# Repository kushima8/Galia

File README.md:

# Galia
Split 61-key ergo keyboard with trackball on right-hand side.

## Disclaimer
The layout is based on the [Ergodash](https://github.com/omkbd/ErgoDash) layout with the inner-most keys removed and a modified thumb cluster on the left hand side, and integrated 34mm trackball on the right. The Pro Micro position was also moved inwards to allow for a thinner board. The Ergodash layout was only used as a reference, nothing was copied and the board is a completely new design. Finally, the mechanical design of the [aball](https://github.com/brickbots/aball) was referenced for the design of the trackball mount, but an entirely new design was created.

## Key Features
* Slim design, or as slim as I could get while using standard MX-style Switches. Essentially, the Pro Micro or whatever other microcontroller used mounts under the PCB, flush and facing up with the help of a cutout.
* SMK MX-style switch support, solder only but the holes are mill-max socket compatible.
* OLED support, either using a standard 0.91" SSD1306 OLED or the [Crenshaw](https://github.com/Ariamelon/Crenshaw) 1.3" OLED breakout board.
* Single rotary encoder position replacing the top-most switch of the left thumb cluster.
* 34mm trackball on the right-hand side using the [Ogen](https://github.com/Ariamelon/Ogen) PMW3360 sensor board. Also compatible with [Jack's](https://www.tindie.com/products/jkicklighter/pmw3360-motion-sensor/) version. 
* Useable in both wired and wireless modes.
* Supports either charger on the microcontroller board or an external TP4056-based charger for faster charging. the TP4056 charger is also flush-mounted sitting up and supports the use of 0305 or 7305 mill-max hotswap sockets if desired.
* Case design with plate included with in-built 10° tent. Plate assumes use of the Crenshaw.
* Supports a massive battery due to the large space in the case. I'm personally using 18650 batteries. Go a year without charging!

## Changelog
* 02/10/2020: Initial commit with case.
* 06/10/2020: Added spot for external TP4056 charger board.
* 10/10/2020: Changed reset switch footprint and position, removed useless pull-up resistor.
* 11/10/2020: Now uses much less plastic and the position of the trackball was moved inwards and downwards.

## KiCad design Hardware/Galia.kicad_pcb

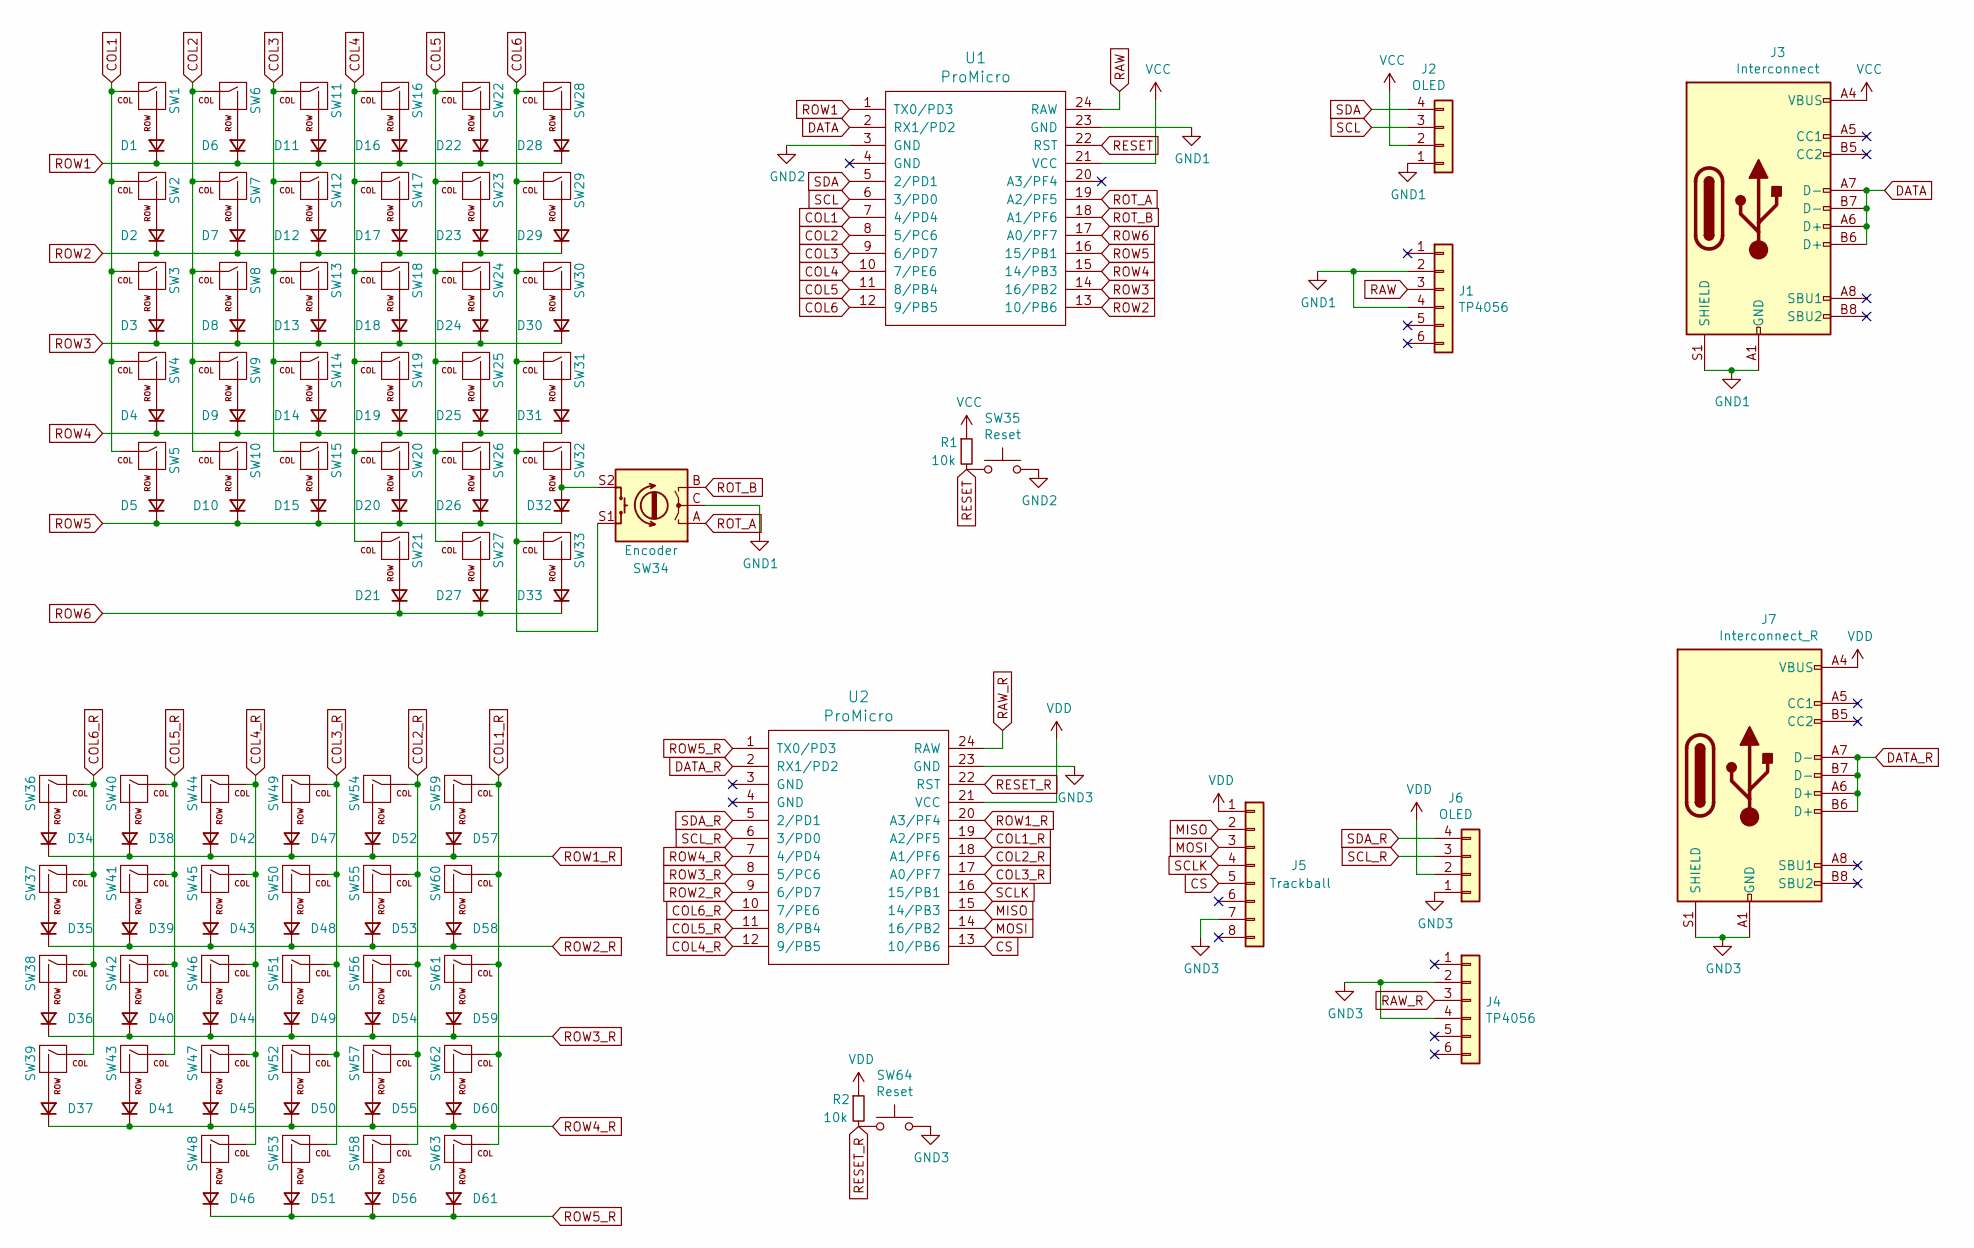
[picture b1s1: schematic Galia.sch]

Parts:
D1, D2, D3, D4, D5, D6, D7, D8, D9, D10, D11, D12, D13, D14, D15, D16, D17, D18, D19, D20, D21, D22, D23, D24, D25, D26, D27, D28, D29, D30, D31, D32, D33, D34, D35, D36, D37, D38, D39, D40, D41, D42, D43, D44, D45, D46, D47, D48, D49, D50, D51, D52, D53, D54, D55, D56, D57, D58, D59, D60, D61: D; D_SOD-123
J1, J4: TP4056; TP4056-18650
J2, J6: OLED; PinHeader_1x04_P2.54mm_Vertical_No_Silk
J3: Interconnect; USB-C-C168688
J5: Trackball; PinHeader_1x08_P2.54mm_Vertical
J7: Interconnect_R; USB-C-C168688
R1, R2: 10k; R_0603_1608Metric_Pad1.05x0.95mm_HandSolder
SW1, SW2, SW3, SW4, SW5, SW6, SW7, SW8, SW9, SW10, SW11, SW12, SW13, SW14, SW15, SW16, SW17, SW18, SW19, SW20, SW21, SW22, SW23, SW24, SW25, SW26, SW27, SW28, SW29, SW30, SW31, SW32, SW33, SW36, SW37, SW38, SW39, SW40, SW41, SW42, SW43, SW44, SW45, SW46, SW47, SW48, SW49, SW50, SW51, SW52, SW53, SW54, SW55, SW56, SW57, SW58, SW59, SW60, SW61, SW62, SW63: MX; CherryMX_Hotswap_SMK
SW34: Encoder; RotaryEncoder_Alps_EC11E-Switch_Vertical_H20mm
SW35, SW64: Reset; Switch_Tactile_SPST_Angled_MJTP1117
U1, U2: ProMicro; ArduinoProMicro_Blank

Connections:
COL1: SW1.1 (COL), SW2.1 (COL), SW3.1 (COL), SW4.1 (COL), SW5.1 (COL), U1.7 (4/PD4)
COL1_R: SW59.1 (COL), SW60.1 (COL), SW61.1 (COL), SW62.1 (COL), SW63.1 (COL), U2.19 (A2/PF5)
COL2: SW6.1 (COL), SW7.1 (COL), SW8.1 (COL), SW9.1 (COL), SW10.1 (COL), U1.8 (5/PC6)
COL2_R: SW54.1 (COL), SW55.1 (COL), SW56.1 (COL), SW57.1 (COL), SW58.1 (COL), U2.18 (A1/PF6)
COL3: SW11.1 (COL), SW12.1 (COL), SW13.1 (COL), SW14.1 (COL), SW15.1 (COL), U1.9 (6/PD7)
COL3_R: SW49.1 (COL), SW50.1 (COL), SW51.1 (COL), SW52.1 (COL), SW53.1 (COL), U2.17 (A0/PF7)
COL4: SW16.1 (COL), SW17.1 (COL), SW18.1 (COL), SW19.1 (COL), SW20.1 (COL), SW21.1 (COL), U1.10 (7/PE6)
COL4_R: SW44.1 (COL), SW45.1 (COL), SW46.1 (COL), SW47.1 (COL), SW48.1 (COL), U2.12 (9/PB5)
COL5: SW22.1 (COL), SW23.1 (COL), SW24.1 (COL), SW25.1 (COL), SW26.1 (COL), SW27.1 (COL), U1.11 (8/PB4)
COL5_R: SW40.1 (COL), SW41.1 (COL), SW42.1 (COL), SW43.1 (COL), U2.11 (8/PB4)
COL6: SW28.1 (COL), SW29.1 (COL), SW30.1 (COL), SW31.1 (COL), SW32.1 (COL), SW33.1 (COL), SW34.S1, U1.12 (9/PB5)
COL6_R: SW36.1 (COL), SW37.1 (COL), SW38.1 (COL), SW39.1 (COL), U2.10 (7/PE6)
CS: J5.5, U2.13 (10/PB6)
DATA: J3.A6 (D+), J3.A7 (D-), J3.B6 (D+), J3.B7 (D-), U1.2 (RX1/PD2)
DATA_R: J7.A6 (D+), J7.A7 (D-), J7.B6 (D+), J7.B7 (D-), U2.2 (RX1/PD2)
GND1: J1.2, J1.4, J2.1, J3.A1 (GND), J3.A12 (GND), J3.B1 (GND), J3.B12 (GND), J3.S1 (SHIELD), SW34.C, U1.23 (GND)
GND2: SW35.2, U1.3 (GND)
GND3: J4.2, J4.4, J5.7, J6.1, J7.A1 (GND), J7.A12 (GND), J7.B1 (GND), J7.B12 (GND), J7.S1 (SHIELD), SW64.2, U2.23 (GND)
MISO: J5.2, U2.15 (14/PB3)
MOSI: J5.3, U2.14 (16/PB2)
unnamed: D1.2 (A), SW1.2 (ROW)
unnamed: D2.2 (A), SW2.2 (ROW)
unnamed: D3.2 (A), SW3.2 (ROW)
unnamed: D4.2 (A), SW4.2 (ROW)
unnamed: D5.2 (A), SW5.2 (ROW)
unnamed: D6.2 (A), SW6.2 (ROW)
unnamed: D7.2 (A), SW7.2 (ROW)
unnamed: D8.2 (A), SW8.2 (ROW)
unnamed: D9.2 (A), SW9.2 (ROW)
unnamed: D10.2 (A), SW10.2 (ROW)
unnamed: D11.2 (A), SW11.2 (ROW)
unnamed: D12.2 (A), SW12.2 (ROW)
unnamed: D13.2 (A), SW13.2 (ROW)
unnamed: D14.2 (A), SW14.2 (ROW)
unnamed: D15.2 (A), SW15.2 (ROW)
unnamed: D16.2 (A), SW16.2 (ROW)
unnamed: D17.2 (A), SW17.2 (ROW)
unnamed: D18.2 (A), SW18.2 (ROW)
unnamed: D19.2 (A), SW19.2 (ROW)
unnamed: D20.2 (A), SW20.2 (ROW)
unnamed: D21.2 (A), SW21.2 (ROW)
unnamed: D22.2 (A), SW22.2 (ROW)
unnamed: D23.2 (A), SW23.2 (ROW)
unnamed: D24.2 (A), SW24.2 (ROW)
unnamed: D25.2 (A), SW25.2 (ROW)
unnamed: D26.2 (A), SW26.2 (ROW)
unnamed: D27.2 (A), SW27.2 (ROW)
unnamed: D28.2 (A), SW28.2 (ROW)
unnamed: D29.2 (A), SW29.2 (ROW)
unnamed: D30.2 (A), SW30.2 (ROW)
unnamed: D31.2 (A), SW31.2 (ROW)
unnamed: D32.2 (A), SW32.2 (ROW), SW34.S2
unnamed: D33.2 (A), SW33.2 (ROW)
unnamed: D34.2 (A), SW36.2 (ROW)
unnamed: D35.2 (A), SW37.2 (ROW)
unnamed: D36.2 (A), SW38.2 (ROW)
unnamed: D37.2 (A), SW39.2 (ROW)
unnamed: D38.2 (A), SW40.2 (ROW)
unnamed: D39.2 (A), SW41.2 (ROW)
unnamed: D40.2 (A), SW42.2 (ROW)
unnamed: D41.2 (A), SW43.2 (ROW)
unnamed: D42.2 (A), SW44.2 (ROW)
unnamed: D43.2 (A), SW45.2 (ROW)
unnamed: D44.2 (A), SW46.2 (ROW)
unnamed: D45.2 (A), SW47.2 (ROW)
unnamed: D46.2 (A), SW48.2 (ROW)
unnamed: D47.2 (A), SW49.2 (ROW)
unnamed: D48.2 (A), SW50.2 (ROW)
unnamed: D49.2 (A), SW51.2 (ROW)
unnamed: D50.2 (A), SW52.2 (ROW)
unnamed: D51.2 (A), SW53.2 (ROW)
unnamed: D52.2 (A), SW54.2 (ROW)
unnamed: D53.2 (A), SW55.2 (ROW)
unnamed: D54.2 (A), SW56.2 (ROW)
unnamed: D55.2 (A), SW57.2 (ROW)
unnamed: D56.2 (A), SW58.2 (ROW)
unnamed: D57.2 (A), SW59.2 (ROW)
unnamed: D58.2 (A), SW60.2 (ROW)
unnamed: D59.2 (A), SW61.2 (ROW)
unnamed: D60.2 (A), SW62.2 (ROW)
unnamed: D61.2 (A), SW63.2 (ROW)
RAW: J1.3, U1.24 (RAW)
RAW_R: J4.3, U2.24 (RAW)
RESET: R1.2, SW35.1, U1.22 (RST)
RESET_R: R2.2, SW64.1, U2.22 (RST)
ROT_A: SW34.A, U1.19 (A2/PF5)
ROT_B: SW34.B, U1.18 (A1/PF6)
ROW1: D1.1 (K), D6.1 (K), D11.1 (K), D16.1 (K), D22.1 (K), D28.1 (K), U1.1 (TX0/PD3)
ROW1_R: D34.1 (K), D38.1 (K), D42.1 (K), D47.1 (K), D52.1 (K), D57.1 (K), U2.20 (A3/PF4)
ROW2: D2.1 (K), D7.1 (K), D12.1 (K), D17.1 (K), D23.1 (K), D29.1 (K), U1.13 (10/PB6)
ROW2_R: D35.1 (K), D39.1 (K), D43.1 (K), D48.1 (K), D53.1 (K), D58.1 (K), U2.9 (6/PD7)
ROW3: D3.1 (K), D8.1 (K), D13.1 (K), D18.1 (K), D24.1 (K), D30.1 (K), U1.14 (16/PB2)
ROW3_R: D36.1 (K), D40.1 (K), D44.1 (K), D49.1 (K), D54.1 (K), D59.1 (K), U2.8 (5/PC6)
ROW4: D4.1 (K), D9.1 (K), D14.1 (K), D19.1 (K), D25.1 (K), D31.1 (K), U1.15 (14/PB3)
ROW4_R: D37.1 (K), D41.1 (K), D45.1 (K), D50.1 (K), D55.1 (K), D60.1 (K), U2.7 (4/PD4)
ROW5: D5.1 (K), D10.1 (K), D15.1 (K), D20.1 (K), D26.1 (K), D32.1 (K), U1.16 (15/PB1)
ROW5_R: D46.1 (K), D51.1 (K), D56.1 (K), D61.1 (K), U2.1 (TX0/PD3)
ROW6: D21.1 (K), D27.1 (K), D33.1 (K), U1.17 (A0/PF7)
SCL: J2.3, U1.6 (3/PD0)
SCLK: J5.4, U2.16 (15/PB1)
SCL_R: J6.3, U2.6 (3/PD0)
SDA: J2.4, U1.5 (2/PD1)
SDA_R: J6.4, U2.5 (2/PD1)
VCC: J2.2, J3.A4 (VBUS), J3.A9 (VBUS), J3.B4 (VBUS), J3.B9 (VBUS), R1.1, U1.21 (VCC)
VDD: J5.1, J6.2, J7.A4 (VBUS), J7.A9 (VBUS), J7.B4 (VBUS), J7.B9 (VBUS), R2.1, U2.21 (VCC)

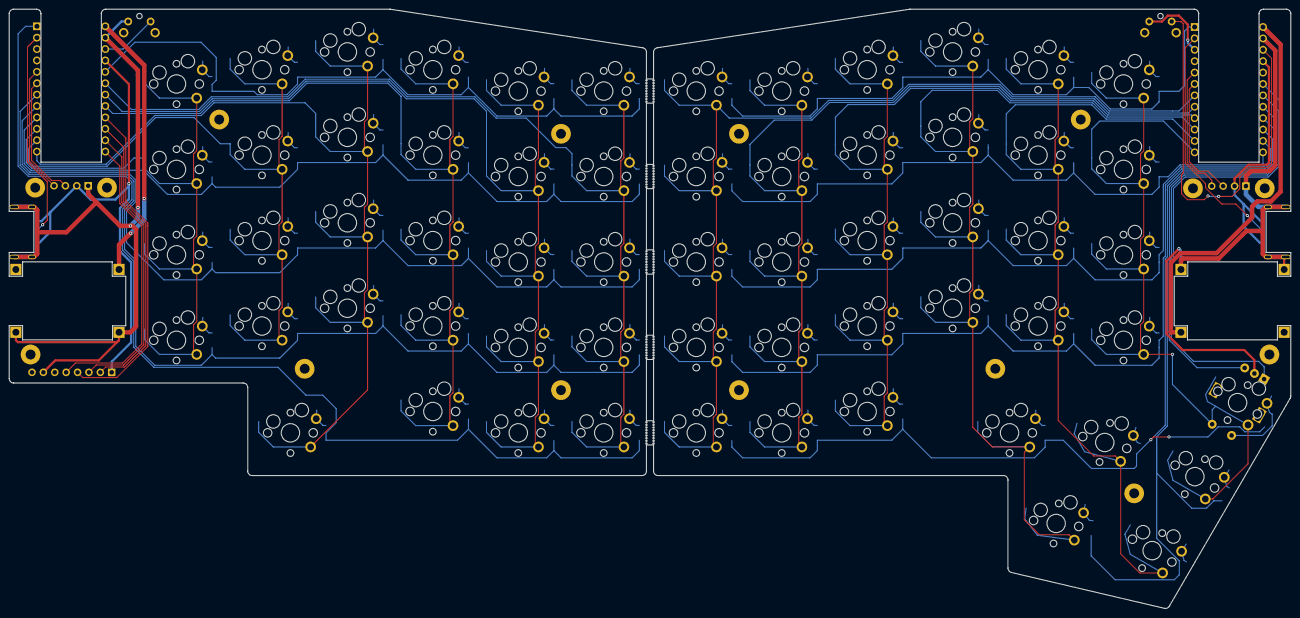
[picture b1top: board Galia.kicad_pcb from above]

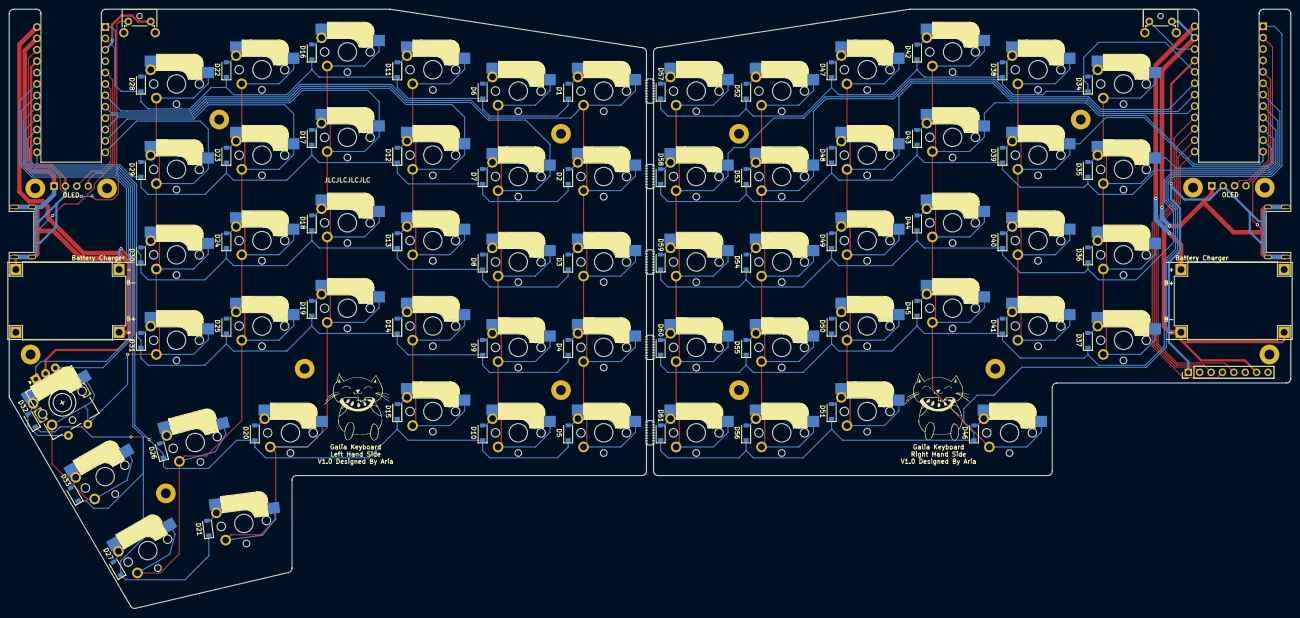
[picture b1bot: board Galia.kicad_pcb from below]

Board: 2 copper layers, 285.7 x 133.6 mm, 136 parts (68 on the bottom side), 105 nets.

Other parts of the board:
G1, G2: Art; Catmelon

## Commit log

2020-10-04 Updated silkscreen
2020-10-05 Added spot for TP4056 charger
2020-10-06 Updated readme and added renders
2020-10-06 Changed readme and added license
2020-10-10 Changed reset switch footprint and position, removed pull-up resistor
2020-10-11 Big update to case
    Now uses much less plastic and the position of the trackball was moved inwards and downwards
2020-10-11 Removed crappy render and updated readme
2020-10-18 Fixed typo
